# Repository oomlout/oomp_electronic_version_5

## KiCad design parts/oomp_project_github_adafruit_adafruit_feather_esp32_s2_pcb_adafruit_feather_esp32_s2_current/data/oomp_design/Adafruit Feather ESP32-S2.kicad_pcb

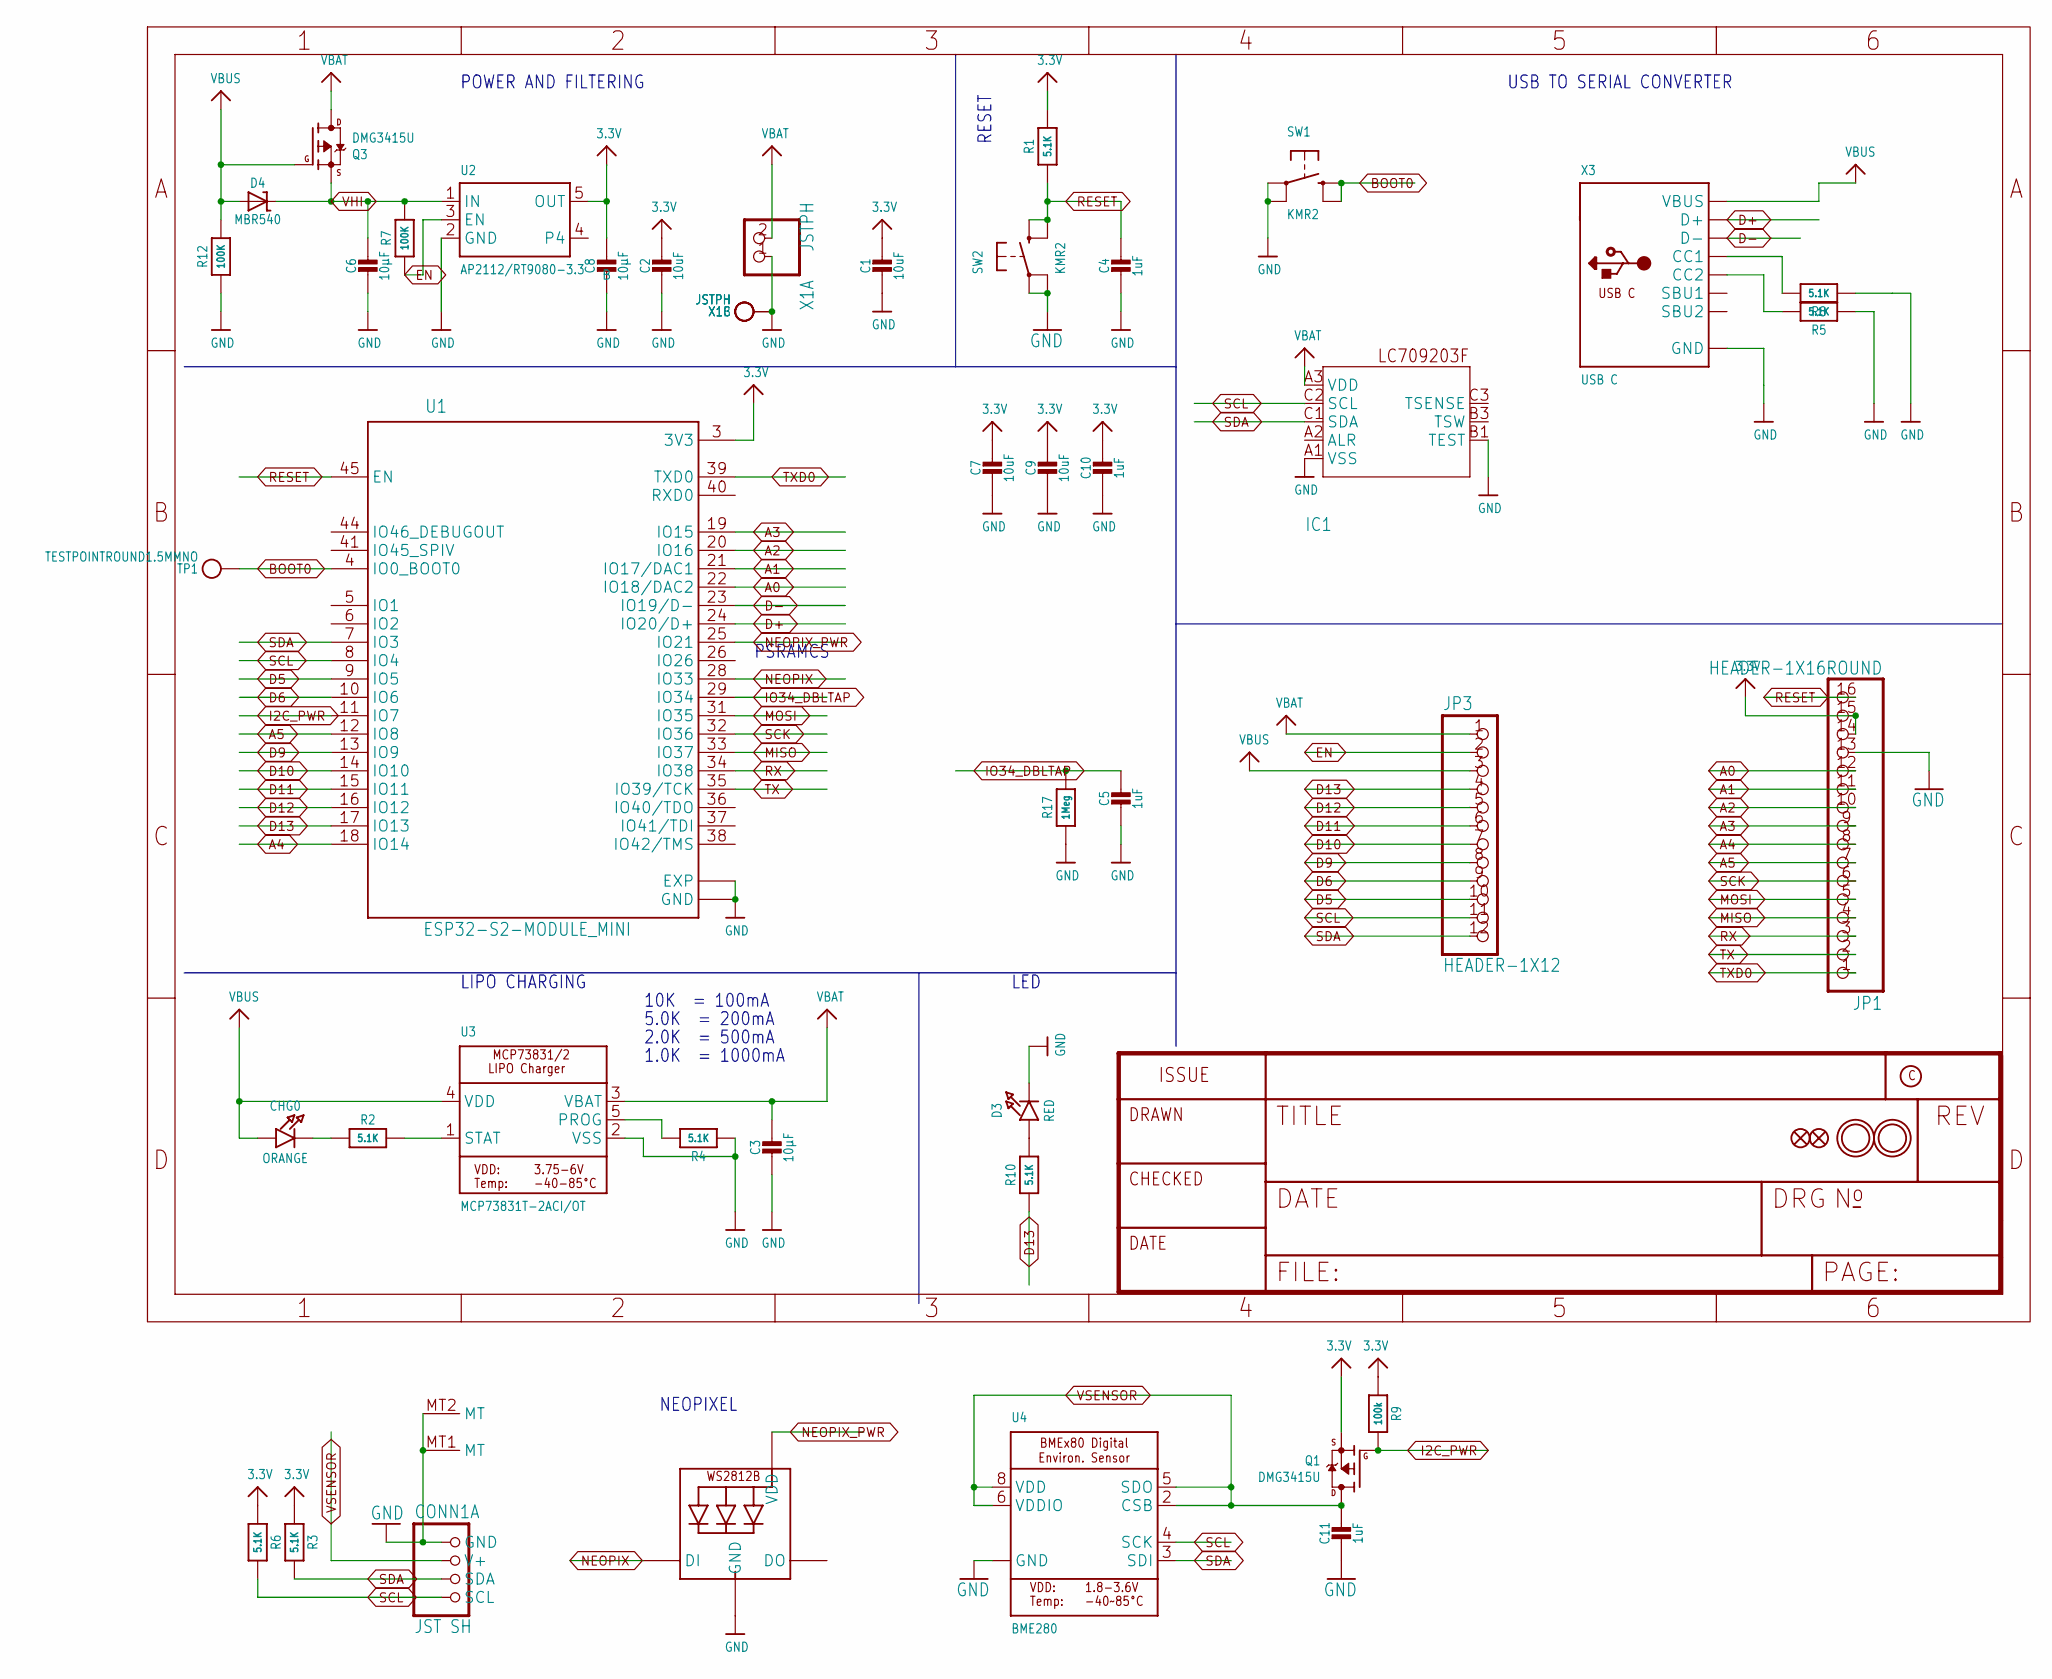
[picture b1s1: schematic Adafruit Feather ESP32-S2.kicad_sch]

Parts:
C1, C2, C7, C9: 10uF; 0805-NO
C3, C6, C8: 10µF; 0805-NO
C4, C5, C10, C11: 1uF; 0603-NO
CHG0: ORANGE; CHIPLED_0603_NOOUTLINE
CONN1: JST SH; JST_SH4_RA
D3: RED; CHIPLED_0603_NOOUTLINE
D4: MBR540; SOD-123
IC1: LC709203F/MH; WLCSP9
JP1: HEADER-1X16ROUND; 1X16_ROUND
JP3: HEADER-1X12; 1X12_ROUND
LED1: WS2812B_SK6805_1515; SK6805_1515
Q1, Q3: DMG3415U; SOT23-R
R1, R2, R3, R4, R5, R6, R8, R10: 5.1K; 0603-NO
R7, R12: 100K; 0603-NO
R9: 100k; 0603-NO
R17: 1Meg; 0603-NO
SW1, SW2: KMR2; BTN_KMR2_4.6X2.8
TP1: TESTPOINTROUND1.5MMNO; TESTPOINT_ROUND_1.5MM_NO
U1: ESP32-S2-MODULE_MINI; QFN60_ESP32-S2-MINI-1_EXP
U2: AP2112/RT9080-3.3; SOT23-5
U3: MCP73831T-2ACI/OT; SOT23-5
U4: BME280
U$31, U$32: MOUNTINGHOLE2.5; MOUNTINGHOLE_2.5_PLATED
U$34, U$35: FIDUCIAL_1MM
X1: JSTPH; JSTPH2_BATT
X3: USB C; USB_C_CUSB31-CFM2AX-01-X

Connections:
3.3V: C1.1, C2.1, C7.1, C8.1, C9.1, C10.1, JP1.14, JP1.15, Q1.2 (S), R1.2, R3.1, R6.1, R9.2, U1.3 (3V3), U2.5 (OUT)
A0: JP1.12, U1.22 (IO18/DAC2)
A1: JP1.11, U1.21 (IO17/DAC1)
A2: JP1.10, U1.20 (IO16)
A3: JP1.9, U1.19 (IO15)
A4: JP1.8, U1.18 (IO14)
A5: JP1.7, U1.12 (IO8)
BOOT0: SW1.B (S), SW1.B' (S1), TP1.P$1, U1.4 (IO0_BOOT0)
D5: JP3.10, U1.9 (IO5)
D6: JP3.9, U1.10 (IO6)
D9: JP3.8, U1.13 (IO9)
D10: JP3.7, U1.14 (IO10)
D11: JP3.6, U1.15 (IO11)
D12: JP3.5, U1.16 (IO12)
D13: JP3.4, R10.1, U1.17 (IO13)
D+: U1.24 (IO20/D+), X3.A6 (D+), X3.B6 (D+)
D-: U1.23 (IO19/D-), X3.A7 (D-), X3.B7 (D-)
EN: JP3.2, R7.1, U2.3 (EN)
GND: C1.2, C2.2, C3.2, C4.2, C5.2, C6.2, C7.2, C8.2, C9.2, C10.2, C11.2, CONN1.1 (GND), CONN1.MT1 (MT), CONN1.MT2 (MT), D3.C, IC1.A1 (VSS), IC1.B1 (TEST), JP1.13, LED1.4 (GND), R4.1, R5.1, R8.1, R12.1, R17.1, SW1.A, SW1.A' (P1), SW2.A, SW2.A' (P1), U1.1 (GND), U1.2 (GND), U1.30 (GND), U1.42 (GND), U1.43 (GND), U1.46 (GND), U1.47 (GND), U1.48 (GND), U1.49 (GND), U1.50 (GND), U1.51 (GND), U1.52 (GND), U1.53 (GND), U1.54 (GND), U1.55 (GND), U1.56 (GND), U1.57 (GND), U1.58 (GND), U1.59 (GND), U1.60 (GND), U1.61 (EXP), U1.62 (EXP), U1.63 (EXP), U1.64 (EXP), U1.65 (EXP), U1.66 (EXP), U1.67 (EXP), U1.68 (EXP), U1.69 (EXP), U1.70 (EXP), U1.71 (EXP), U1.72 (EXP), U1.73 (EXP), U2.2 (GND), U3.2 (VSS), U4.1 (GND), U4.7 (GND), X1.1, X1.NC1, X1.NC2, X3.A1B12 (GND), X3.B1A12 (GND)
I2C_PWR: Q1.1 (G), R9.1, U1.11 (IO7)
IO34_DBLTAP: C5.1, R17.2, U1.29 (IO34)
MISO: JP1.4, U1.33 (IO37)
MOSI: JP1.5, U1.31 (IO35)
unnamed: CHG0.C, R2.1
unnamed: R2.2, U3.1 (STAT)
unnamed: R4.2, U3.5 (PROG)
unnamed: D3.A, R10.2
unnamed: R8.2, X3.A5 (CC1)
unnamed: R5.2, X3.B5 (CC2)
NEOPIX: LED1.1 (DI), U1.28 (IO33)
NEOPIX_PWR: LED1.2 (VDD), U1.25 (IO21)
RESET: C4.1, JP1.16, R1.1, SW2.B (S), SW2.B' (S1), U1.45 (EN)
RX: JP1.3, U1.34 (IO38)
SCK: JP1.6, U1.32 (IO36)
SCL: CONN1.4 (SCL), IC1.C2 (SCL), JP3.11, R6.2, U1.8 (IO4), U4.4 (SCK)
SDA: CONN1.3 (SDA), IC1.C1 (SDA), JP3.12, R3.2, U1.7 (IO3), U4.3 (SDI)
TX: JP1.2, U1.35 (IO39/TCK)
TXD0: JP1.1, U1.39 (TXD0)
VBAT: C3.1, IC1.A3 (VDD), JP3.1, Q3.3 (D), U3.3 (VBAT), X1.2
VBUS: CHG0.A, D4.A, JP3.3, Q3.1 (G), R12.2, U3.4 (VDD), X3.A4B9 (VBUS), X3.B4A9 (VBUS)
VHI: C6.1, D4.C, Q3.2 (S), R7.2, U2.1 (IN)
VSENSOR: C11.1, CONN1.2 (V+), Q1.3 (D), U4.2 (CSB), U4.5 (SDO), U4.6 (VDDIO), U4.8 (VDD)

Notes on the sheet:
1.0K = 1000mA
NEOPIXEL
5.0K = 200mA
LED
USB TO SERIAL CONVERTER
LIPO CHARGING
POWER AND FILTERING
2.0K = 500mA
10K = 100mA
RESET
PSRAMCS

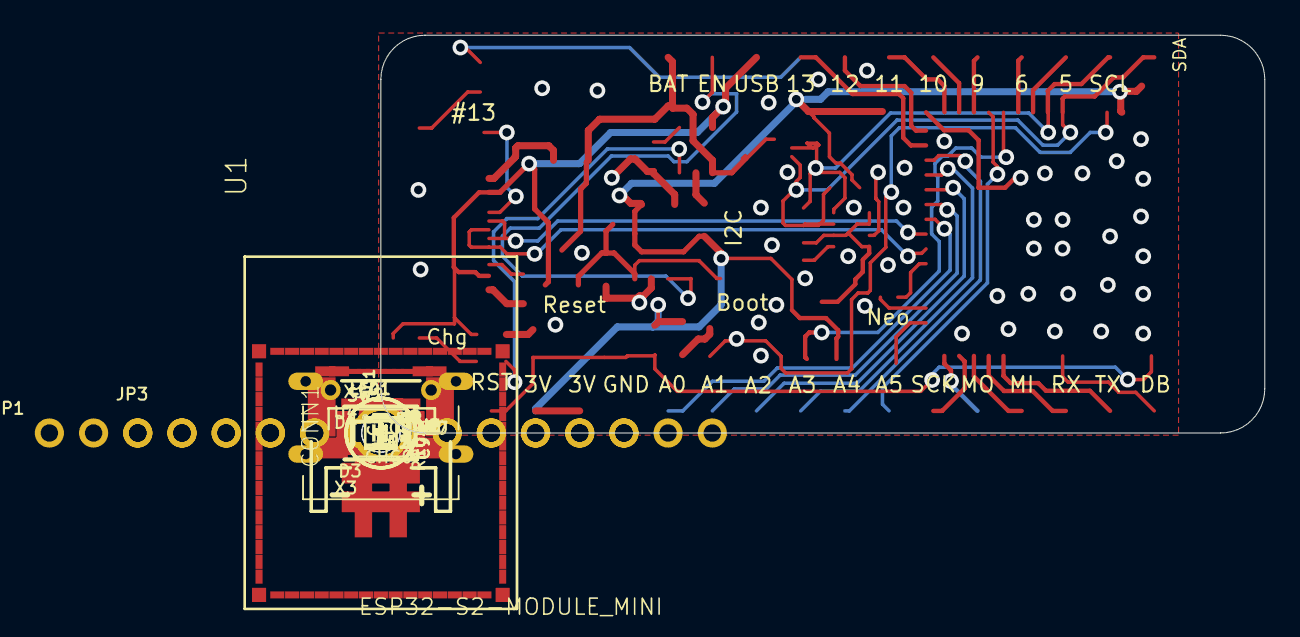
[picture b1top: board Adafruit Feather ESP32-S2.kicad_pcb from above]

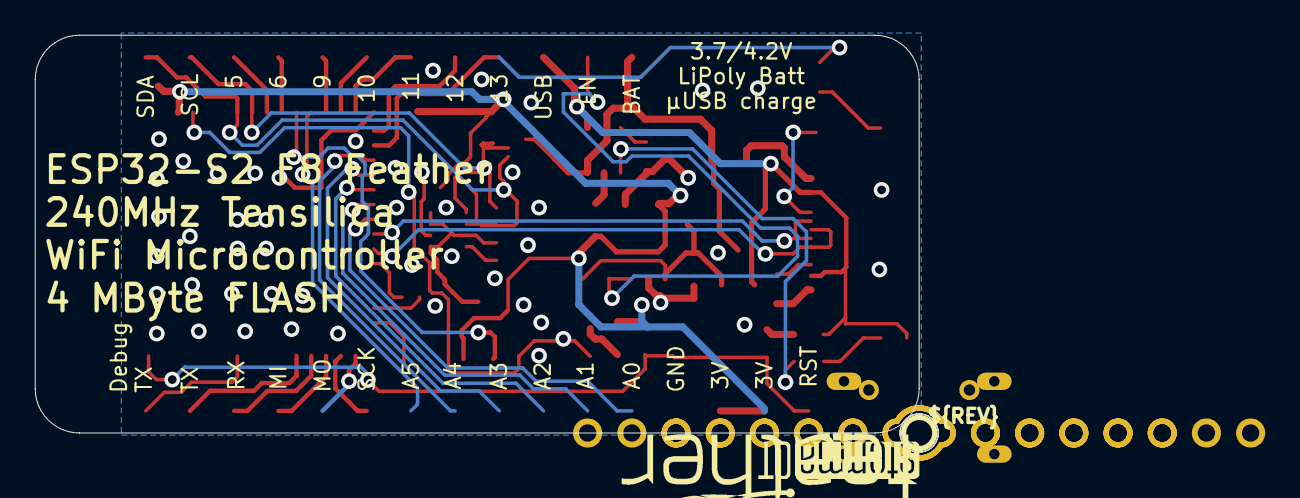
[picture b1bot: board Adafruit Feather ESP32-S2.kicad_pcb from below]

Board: 2 copper layers, 50.8 x 22.9 mm, 51 parts (4 on the bottom side), 42 nets.

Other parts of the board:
U$14: PCBFEAT-REV-040
U$15: FEATHERLOGO_MED
U$53: STEMMAQT
UNK_HOLE_0: dummyfp0
UNK_HOLE_1: dummyfp1

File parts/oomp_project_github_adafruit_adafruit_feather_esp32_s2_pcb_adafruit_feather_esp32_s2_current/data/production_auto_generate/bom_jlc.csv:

Comment,Designator,Footprint,LCSC Part #
,JP3,Adafruit Feather ESP32-S2-import-fps:1X12_ROUND,C7501588
,JP1,Adafruit Feather ESP32-S2-import-fps:1X16_ROUND,C7501270
,U$15,Adafruit Feather ESP32-S2-import-fps:FEATHERLOGO_MED,
,U$14,Adafruit Feather ESP32-S2-import-fps:PCBFEAT-REV-040,
,U$53,Adafruit Feather ESP32-S2-import-fps:STEMMAQT,
,TP1,Adafruit Feather ESP32-S2-import-fps:TESTPOINT_ROUND_1.5MM_NO,
100K,"R7,R12",Adafruit Feather ESP32-S2-import-fps:0603-NO,C25803
100k,R9,Adafruit Feather ESP32-S2-import-fps:0603-NO,C25803
10uF,"C1,C2,C7,C9",Adafruit Feather ESP32-S2-import-fps:0805-NO,
10µF,"C3,C6,C8",Adafruit Feather ESP32-S2-import-fps:0805-NO,
1Meg,R17,Adafruit Feather ESP32-S2-import-fps:0603-NO,C2907003
1uF,"C4,C5,C10,C11",Adafruit Feather ESP32-S2-import-fps:0603-NO,C5673
5.1K,"R1,R2,R3,R4,R5,R6,R8,R10",Adafruit Feather ESP32-S2-import-fps:0603-NO,C23186
AP2112/RT9080-3.3,U2,Adafruit Feather ESP32-S2-import-fps:SOT23-5,
BME280,U4,Adafruit Feather ESP32-S2-import-fps:BME280,
DMG3415U,"Q1,Q3",Adafruit Feather ESP32-S2-import-fps:SOT23-R,
ESP32-S2-MODULE_MINI,U1,Adafruit Feather ESP32-S2-import-fps:QFN60_ESP32-S2-MINI-1_EXP,
FIDUCIAL_1MM,"U$34,U$35",Adafruit Feather ESP32-S2-import-fps:FIDUCIAL_1MM,
JST SH,CONN1,Adafruit Feather ESP32-S2-import-fps:JST_SH4_RA,
JSTPH,X1,Adafruit Feather ESP32-S2-import-fps:JSTPH2_BATT,
KMR2,"SW1,SW2",Adafruit Feather ESP32-S2-import-fps:BTN_KMR2_4.6X2.8,
LC709203F/MH,IC1,Adafruit Feather ESP32-S2-import-fps:WLCSP9,
MBR540,D4,Adafruit Feather ESP32-S2-import-fps:SOD-123,
MCP73831T-2ACI/OT,U3,Adafruit Feather ESP32-S2-import-fps:SOT23-5,
ORANGE,CHG0,Adafruit Feather ESP32-S2-import-fps:CHIPLED_0603_NOOUTLINE,
RED,D3,Adafruit Feather ESP32-S2-import-fps:CHIPLED_0603_NOOUTLINE,
USB C,X3,Adafruit Feather ESP32-S2-import-fps:USB_C_CUSB31-CFM2AX-01-X,
WS2812B_SK6805_1515,LED1,Adafruit Feather ESP32-S2-import-fps:SK6805_1515,

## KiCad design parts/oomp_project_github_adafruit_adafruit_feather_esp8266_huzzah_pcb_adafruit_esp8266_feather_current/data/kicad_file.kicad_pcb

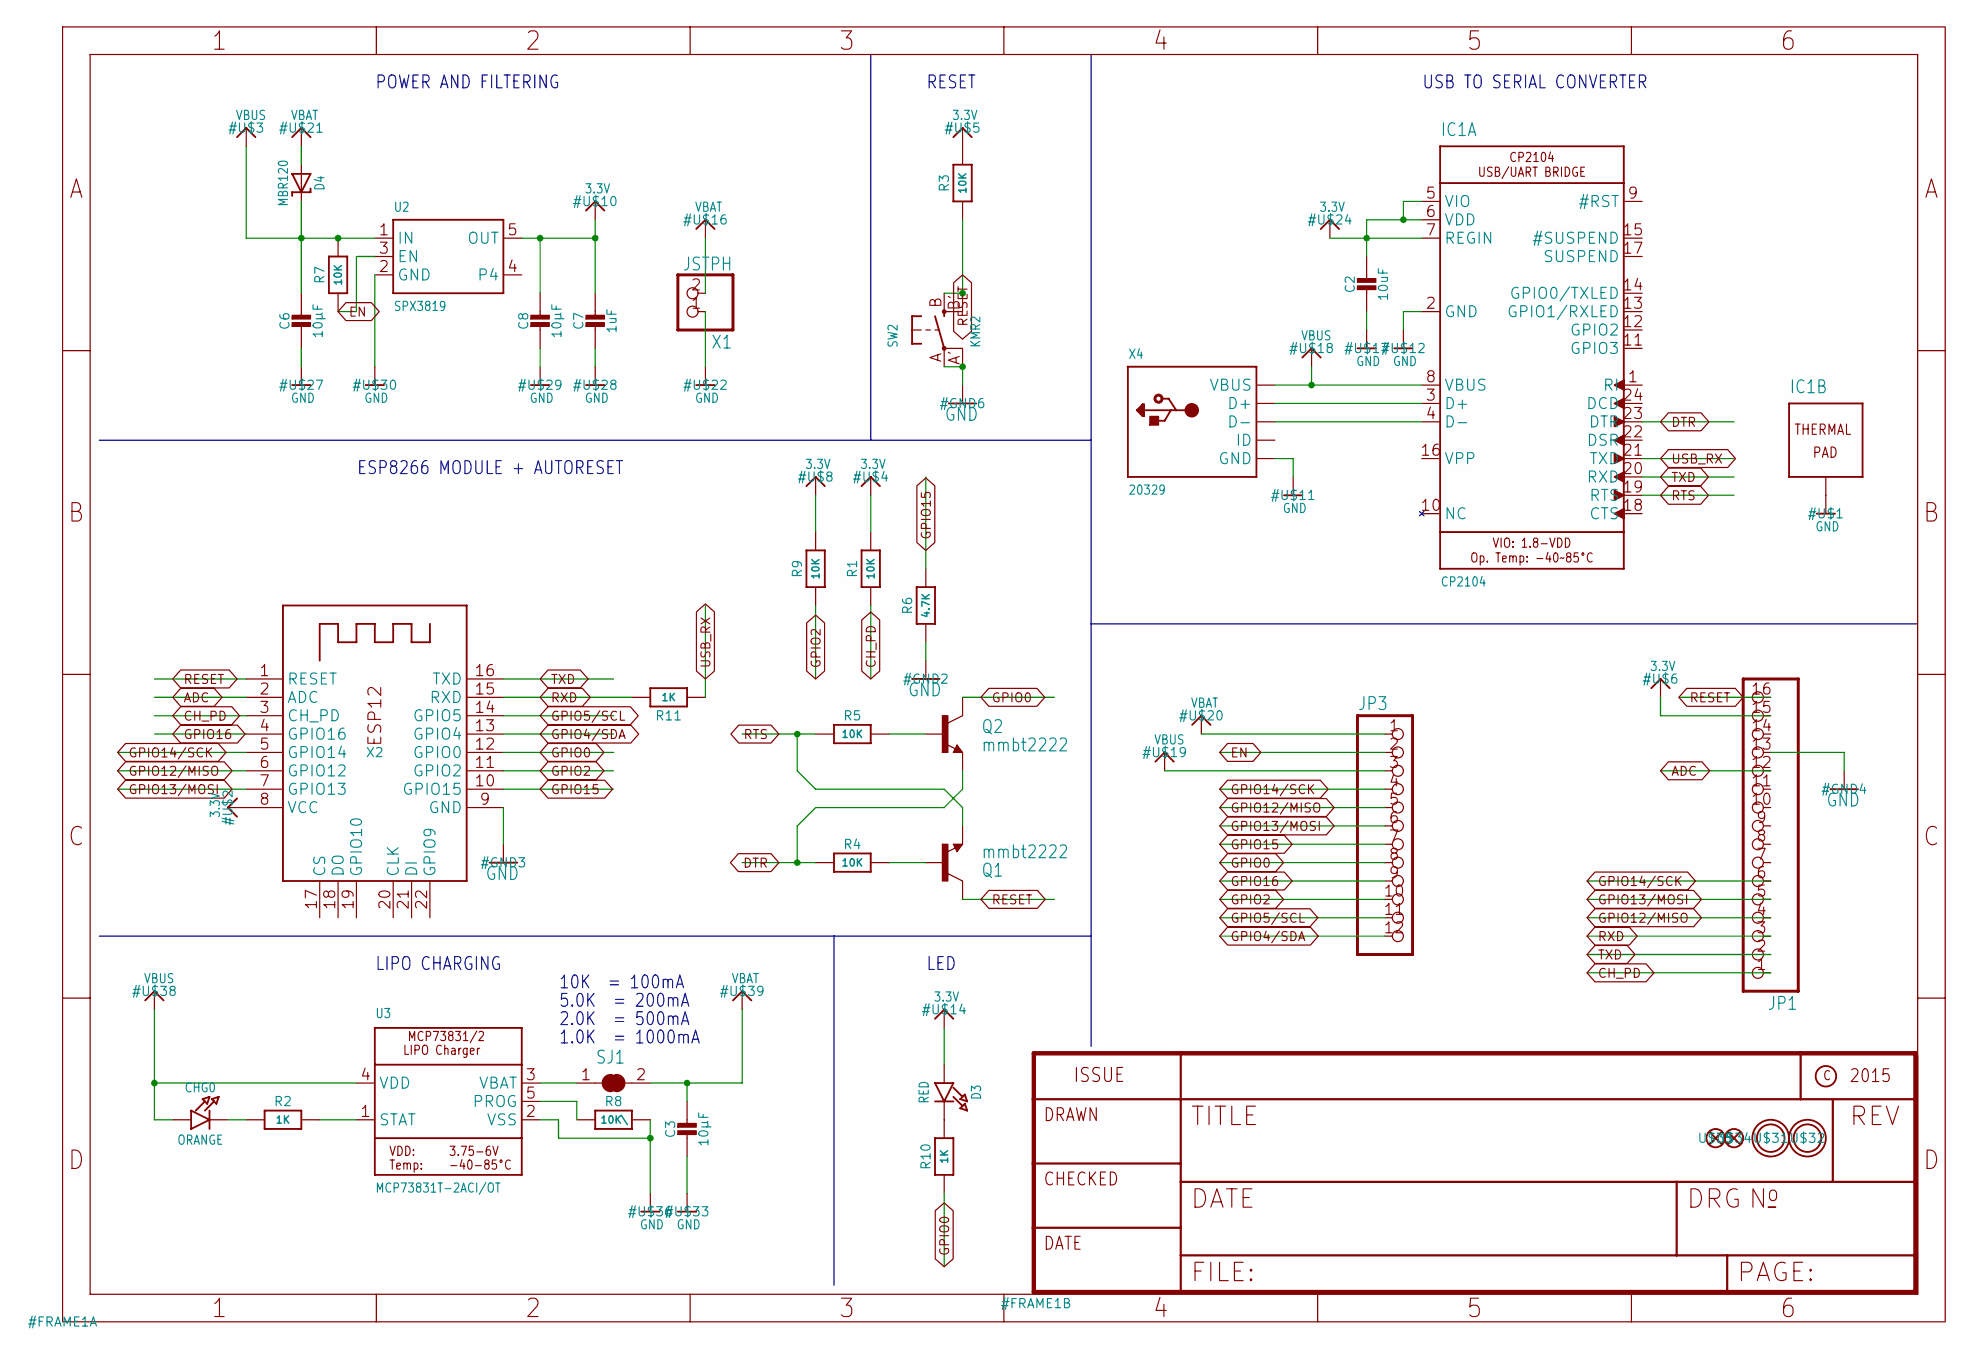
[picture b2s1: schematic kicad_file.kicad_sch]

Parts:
C2: 10uF; 0805-NO
C3, C6, C8: 10µF; 0805-NO
C7: 1uF; 0603-NO
CHG0: ORANGE; CHIPLED_0805_NOOUTLINE
D3: RED; CHIPLED_0805_NOOUTLINE
D4: MBR120; SOD-123
IC1: CP2104; QFN24_4MM_SMSC
JP1: HEADER-1X16ROUND; 1X16_ROUND
JP3: HEADER-1X12; 1X12_ROUND
Q1, Q2: mmbt2222; SOT23-3
R1, R3, R4, R7, R9: 10K; 0603-NO
R2, R10: 1K; 0603-NO
R5: 10K; _0603MP
R6: 4.7K; 0603-NO
R8: 10K\; 0603-NO
R11: 1K; _0603MP
SJ1: SOLDERJUMPER_CLOSED; SOLDERJUMPER_CLOSEDWIRE
SW2: KMR2; BTN_KMR2_4.6X2.8
U2: SPX3819; SOT23-5
U3: MCP73831T-2ACI/OT; SOT23-5
U$31, U$32: MOUNTINGHOLE2.5; MOUNTINGHOLE_2.5_PLATED
U$34, U$35: FIDUCIAL""; FIDUCIAL_1MM
X1: JSTPH; JSTPH2
X2: ESP-12; ESP-12E
X4: 20329; 4UCONN_20329_V2

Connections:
3.3V: C2.1, C7.1, C8.1, D3.A, IC1.5 (VIO), IC1.6 (VDD), IC1.7 (REGIN), JP1.15, R1.2, R3.2, R9.2, U2.5 (OUT), X2.8 (VCC)
ADC: JP1.12, X2.2 (ADC)
CH_PD: JP1.1, R1.1, X2.3 (CH_PD)
DTR: IC1.23 (DTR), Q2.2 (E), R4.1
EN: JP3.2, R7.1, U2.3 (EN)
GND: C2.2, C3.2, C6.2, C7.2, C8.2, IC1.2 (GND), IC1.THERM (TP), JP1.13, R6.1, R8.2, SW2.A, SW2.A' (P1), U2.2 (GND), U3.2 (VSS), X1.1, X2.9 (GND), X4.BASE@1 (GND), X4.BASE@2 (GND), X4.GND, X4.SPRT@1 (GND), X4.SPRT@2 (GND), X4.SPRT@3 (GND), X4.SPRT@4 (GND)
GPIO0: JP3.8, Q2.3 (C), R10.1, X2.12 (GPIO0)
GPIO2: JP3.10, R9.1, X2.11 (GPIO2)
GPIO4/SDA: JP3.12, X2.13 (GPIO4)
GPIO5/SCL: JP3.11, X2.14 (GPIO5)
GPIO12/MISO: JP1.4, JP3.5, X2.6 (GPIO12)
GPIO13/MOSI: JP1.5, JP3.6, X2.7 (GPIO13)
GPIO14/SCK: JP1.6, JP3.4, X2.5 (GPIO14)
GPIO15: JP3.7, R6.2, X2.10 (GPIO15)
GPIO16: JP3.9, X2.4 (GPIO16)
unnamed: CHG0.C, R2.1
unnamed: IC1.3 (D+), X4.D+
unnamed: R2.2, U3.1 (STAT)
unnamed: R8.1, U3.5 (PROG)
unnamed: D3.C, R10.2
unnamed: IC1.4 (D-), X4.D-
unnamed: SJ1.1, U3.3 (VBAT)
unnamed: Q1.1 (B), R4.2
unnamed: Q2.1 (B), R5.2
RESET: JP1.16, Q1.3 (C), R3.1, SW2.B (S), SW2.B' (S1), X2.1 (RESET)
RTS: IC1.19 (RTS), Q1.2 (E), R5.1
RXD: JP1.3, R11.2, X2.15 (RXD)
TXD: IC1.20 (RXD), JP1.2, X2.16 (TXD)
USB_RX: IC1.21 (TXD), R11.1
VBAT: C3.1, D4.A, JP3.1, SJ1.2, X1.2
VBUS: C6.1, CHG0.A, D4.C, IC1.8 (VBUS), JP3.3, R7.2, U2.1 (IN), U3.4 (VDD), X4.VBUS

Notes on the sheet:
5.0K = 200mA
POWER AND FILTERING
LIPO CHARGING
LED
1.0K = 1000mA
10K = 100mA
USB TO SERIAL CONVERTER
ESP8266 MODULE + AUTORESET
RESET
2.0K = 500mA

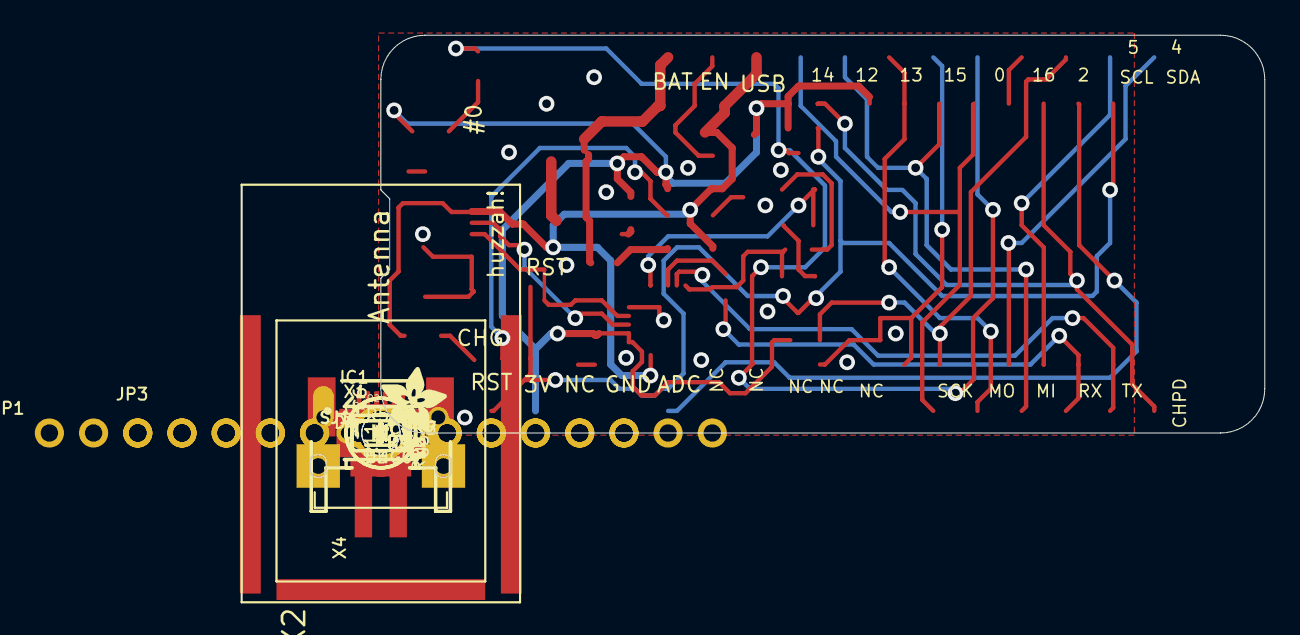
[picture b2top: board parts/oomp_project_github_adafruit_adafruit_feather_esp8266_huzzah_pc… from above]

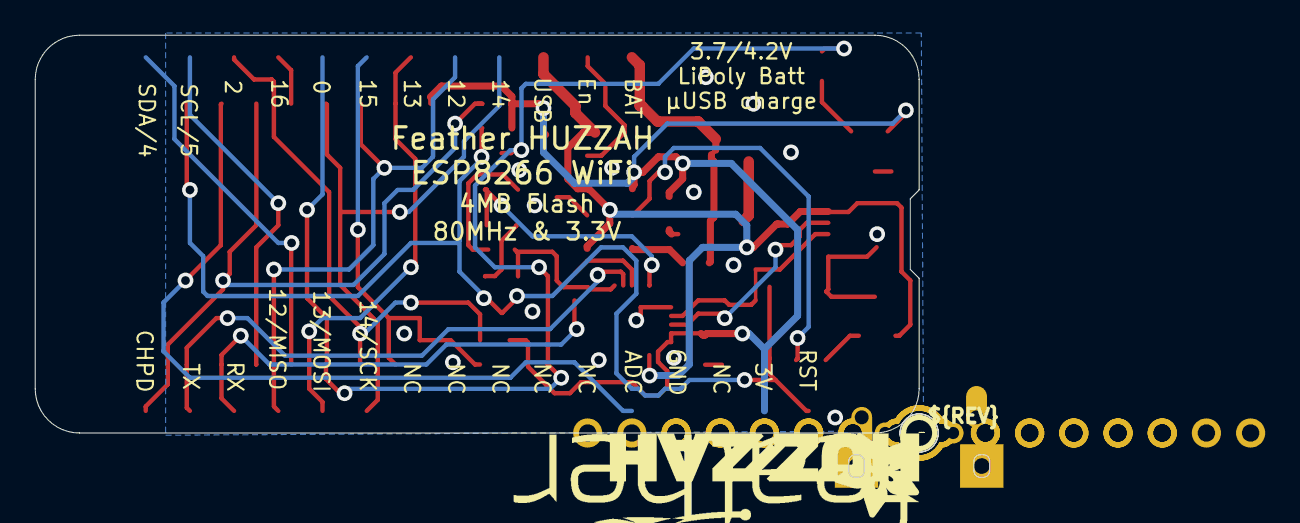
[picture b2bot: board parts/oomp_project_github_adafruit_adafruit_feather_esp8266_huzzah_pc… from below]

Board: 2 copper layers, 50.8 x 22.9 mm, 42 parts (4 on the bottom side), 31 nets.

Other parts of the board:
U$7: ADAFRUIT_5MM
U$9: FEATHERLOGO
U$13: PCBFEAT-REV-040
U$15: ADAFRUIT_3.5MM
U$23: HUZZAHLOGO
UNK_HOLE_0: dummyfp0
UNK_HOLE_1: dummyfp1

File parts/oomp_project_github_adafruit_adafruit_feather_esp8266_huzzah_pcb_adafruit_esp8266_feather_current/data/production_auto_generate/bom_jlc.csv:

Comment,Designator,Footprint,LCSC Part #
,JP3,Adafruit ESP8266 Feather-import-fps:1X12_ROUND,C7501588
,JP1,Adafruit ESP8266 Feather-import-fps:1X16_ROUND,C7501270
,U$15,Adafruit ESP8266 Feather-import-fps:ADAFRUIT_3.5MM,
,U$7,Adafruit ESP8266 Feather-import-fps:ADAFRUIT_5MM,
,U$9,Adafruit ESP8266 Feather-import-fps:FEATHERLOGO,
,U$23,Adafruit ESP8266 Feather-import-fps:HUZZAHLOGO,
,U$13,Adafruit ESP8266 Feather-import-fps:PCBFEAT-REV-040,
10K,"R1,R3,R4,R7,R9",Adafruit ESP8266 Feather-import-fps:0603-NO,C98220
10K,R5,Adafruit ESP8266 Feather-import-fps:_0603MP,C98220
10K\,R8,Adafruit ESP8266 Feather-import-fps:0603-NO,C98220
10uF,C2,Adafruit ESP8266 Feather-import-fps:0805-NO,
10µF,"C3,C6,C8",Adafruit ESP8266 Feather-import-fps:0805-NO,
1K,"R2,R10",Adafruit ESP8266 Feather-import-fps:0603-NO,C2907002
1K,R11,Adafruit ESP8266 Feather-import-fps:_0603MP,C2907002
1uF,C7,Adafruit ESP8266 Feather-import-fps:0603-NO,C5673
20329,X4,Adafruit ESP8266 Feather-import-fps:4UCONN_20329_V2,
4.7K,R6,Adafruit ESP8266 Feather-import-fps:0603-NO,C23162
CP2104,IC1,Adafruit ESP8266 Feather-import-fps:QFN24_4MM_SMSC,
ESP-12,X2,Adafruit ESP8266 Feather-import-fps:ESP-12E,
"FIDUCIAL""""","U$34,U$35",Adafruit ESP8266 Feather-import-fps:FIDUCIAL_1MM,
JSTPH,X1,Adafruit ESP8266 Feather-import-fps:JSTPH2,
KMR2,SW2,Adafruit ESP8266 Feather-import-fps:BTN_KMR2_4.6X2.8,
MBR120,D4,Adafruit ESP8266 Feather-import-fps:SOD-123,
MCP73831T-2ACI/OT,U3,Adafruit ESP8266 Feather-import-fps:SOT23-5,
mmbt2222,"Q1,Q2",Adafruit ESP8266 Feather-import-fps:SOT23-3,
ORANGE,CHG0,Adafruit ESP8266 Feather-import-fps:CHIPLED_0805_NOOUTLINE,
RED,D3,Adafruit ESP8266 Feather-import-fps:CHIPLED_0805_NOOUTLINE,
SPX3819,U2,Adafruit ESP8266 Feather-import-fps:SOT23-5,

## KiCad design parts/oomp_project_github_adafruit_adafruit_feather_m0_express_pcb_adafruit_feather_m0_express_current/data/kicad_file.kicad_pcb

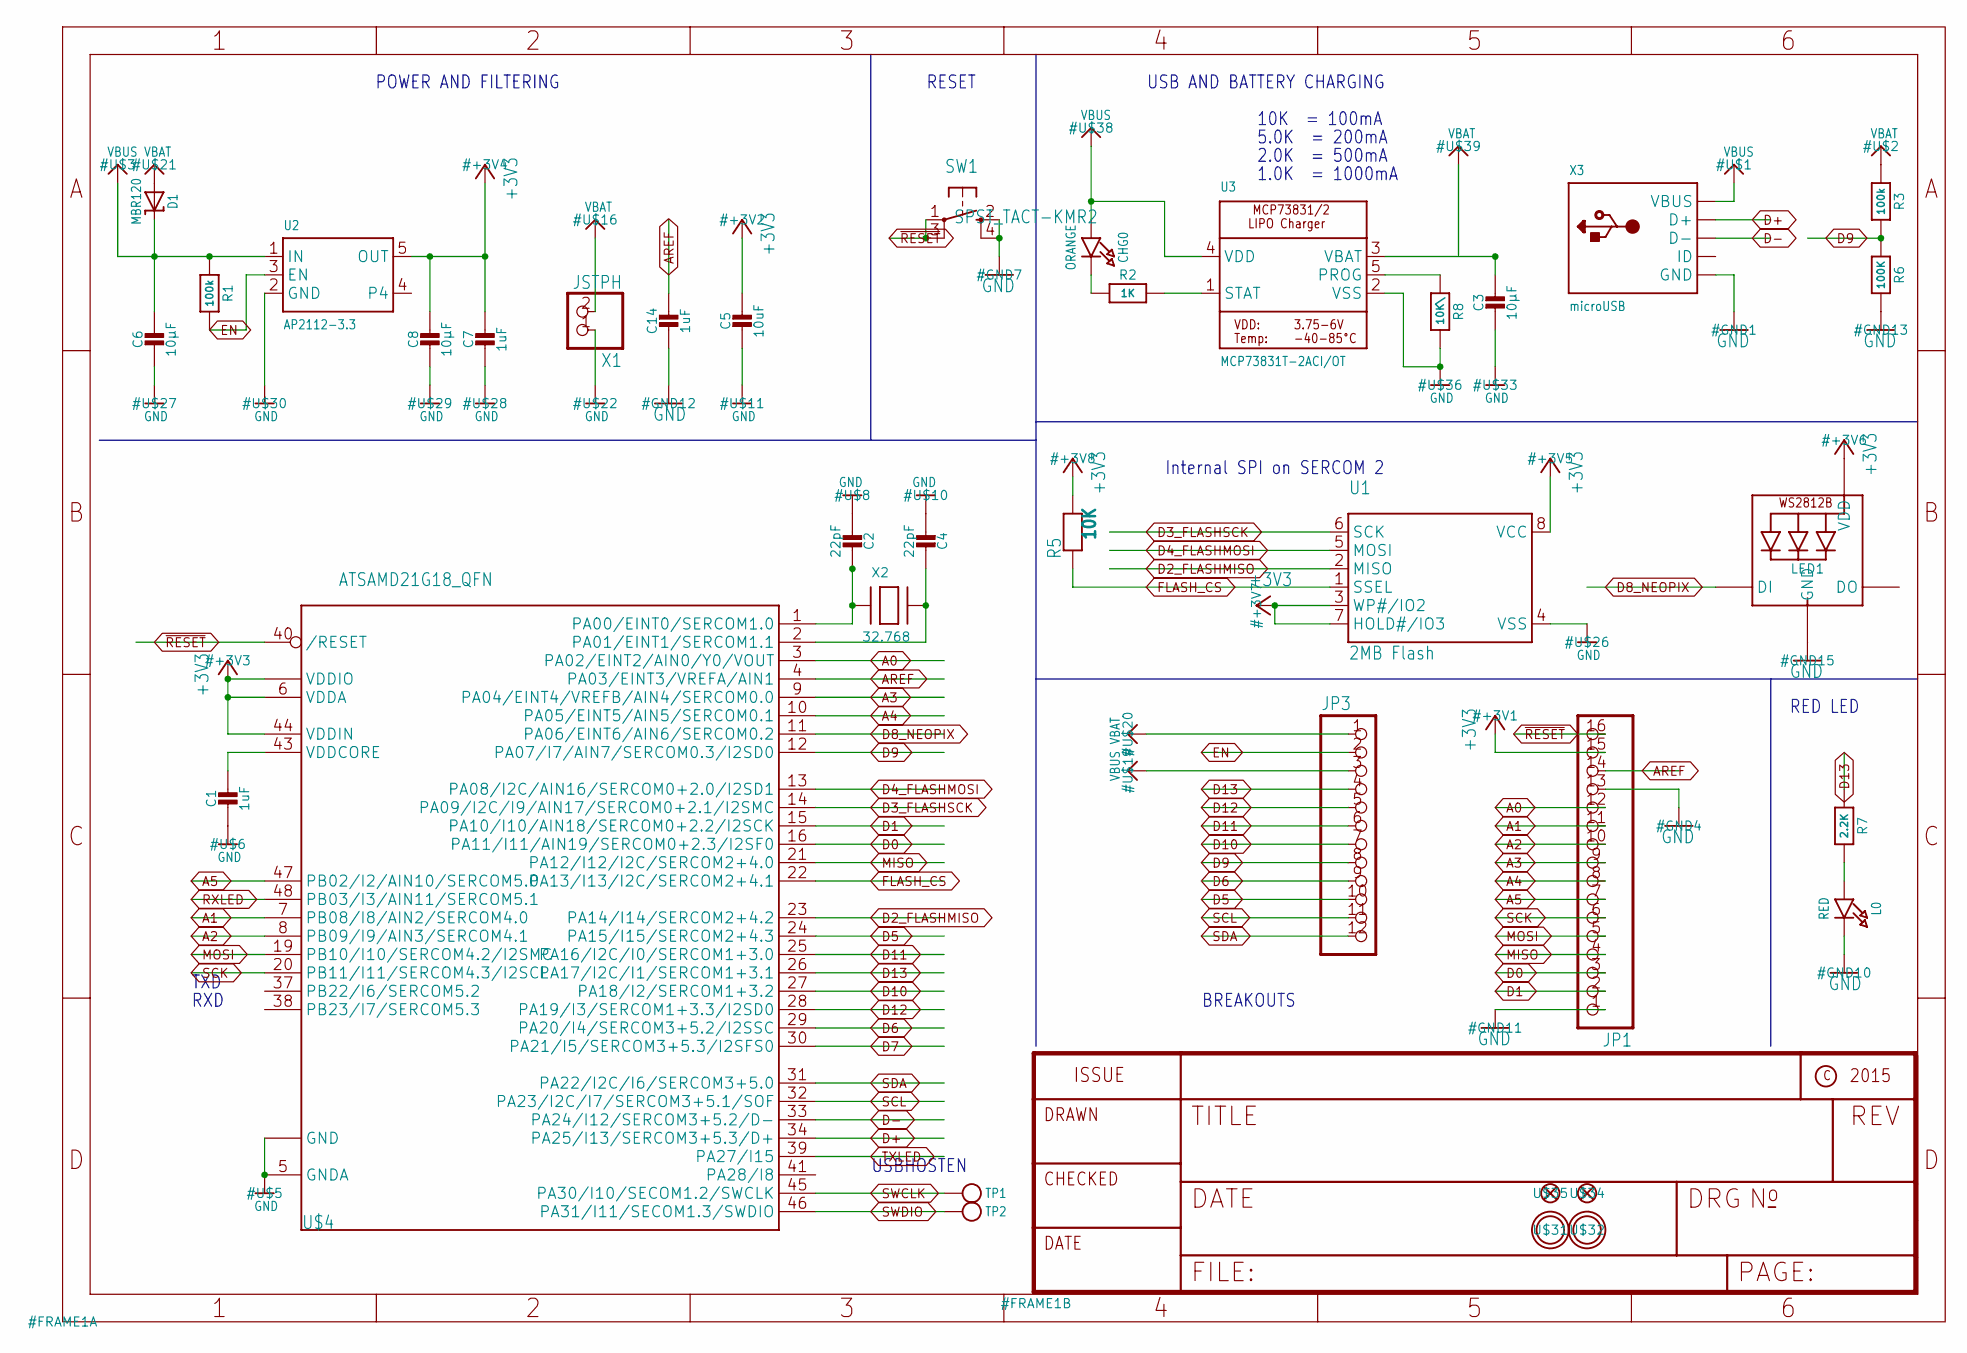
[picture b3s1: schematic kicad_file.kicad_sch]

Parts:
C1, C7, C14: 1uF; 0603-NO
C2, C4: 22pF; 0603-NO
C3, C6, C8: 10µF; 0805-NO
C5: 10uF; 0805-NO
CHG0: ORANGE; CHIPLED_0805_NOOUTLINE
D1: MBR120; SOD-123
JP1: HEADER-1X16ROUND; 1X16_ROUND
JP3: HEADER-1X12; 1X12_ROUND
L0: RED; CHIPLED_0805_NOOUTLINE
LED1: WS2812B3535; LED3535
R1, R3: 100k; 0603-NO
R2: 1K; 0603-NO
R5: 10K; 0603-NO
R6: 100K; 0603-NO
R7: 2.2K; 0603-NO
R8: 10K\; 0603-NO
SW1: SPST_TACT-KMR2; KMR2
TP1, TP2: TESTPOINTROUND1.5MM; TESTPOINT_ROUND_1.5MM
U1: 2MB Flash; SOIC8_208MIL
U2: AP2112-3.3; SOT23-5
U3: MCP73831T-2ACI/OT; SOT23-5
U$4: ATSAMD21G18_QFN; TQFN48_7MM
U$31, U$32: MOUNTINGHOLE2.5; MOUNTINGHOLE_2.5_PLATED
U$34, U$35: FIDUCIAL""; FIDUCIAL_1MM
X1: JSTPH; JSTPH2
X2: 32.768; XTAL3215
X3: microUSB; 4UCONN_20329_V2

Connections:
+3V3: C5.1, C7.1, C8.1, JP1.15, LED1.2 (VDD), R5.2, U1.3 (WP#/IO2), U1.7 (HOLD#/IO3), U1.8 (VCC), U2.5 (OUT), U$4.6 (VDDA), U$4.17 (VDDIO), U$4.36 (VDDIO), U$4.44 (VDDIN)
A0: JP1.12, U$4.3 (PA02/EINT2/AIN0/Y0/VOUT)
A1: JP1.11, U$4.7 (PB08/I8/AIN2/SERCOM4.0)
A2: JP1.10, U$4.8 (PB09/I9/AIN3/SERCOM4.1)
A3: JP1.9, U$4.9 (PA04/EINT4/VREFB/AIN4/SERCOM0.0)
A4: JP1.8, U$4.10 (PA05/EINT5/AIN5/SERCOM0.1)
A5: JP1.7, U$4.47 (PB02/I2/AIN10/SERCOM5.0)
AREF: C14.1, JP1.14, U$4.4 (PA03/EINT3/VREFA/AIN1)
D0: JP1.3, U$4.16 (PA11/I11/AIN19/SERCOM0+2.3/I2SF0)
D1: JP1.2, U$4.15 (PA10/I10/AIN18/SERCOM0+2.2/I2SCK)
D2_FLASHMISO: U1.2 (MISO), U$4.23 (PA14/I14/SERCOM2+4.2)
D3_FLASHSCK: U1.6 (SCK), U$4.14 (PA09/I2C/I9/AIN17/SERCOM0+2.1/I2SMC)
D4_FLASHMOSI: U1.5 (MOSI), U$4.13 (PA08/I2C/AIN16/SERCOM0+2.0/I2SD1)
D5: JP3.10, U$4.24 (PA15/I15/SERCOM2+4.3)
D6: JP3.9, U$4.29 (PA20/I4/SERCOM3+5.2/I2SSC)
D7: U$4.30 (PA21/I5/SERCOM3+5.3/I2SFS0)
D8_NEOPIX: LED1.1 (DI), U$4.11 (PA06/EINT6/AIN6/SERCOM0.2)
D9: JP3.8, R3.2, R6.1, U$4.12 (PA07/I7/AIN7/SERCOM0.3/I2SD0)
D10: JP3.7, U$4.27 (PA18/I2/SERCOM1+3.2)
D11: JP3.6, U$4.25 (PA16/I2C/I0/SERCOM1+3.0)
D12: JP3.5, U$4.28 (PA19/I3/SERCOM1+3.3/I2SD0)
D13: JP3.4, R7.1, U$4.26 (PA17/I2C/I1/SERCOM1+3.1)
D+: U$4.34 (PA25/I13/SERCOM3+5.3/D+), X3.D+
D-: U$4.33 (PA24/I12/SERCOM3+5.2/D-), X3.D-
EN: JP3.2, R1.2, U2.3 (EN)
FLASH_CS: R5.1, U1.1 (SSEL), U$4.22 (PA13/I13/I2C/SERCOM2+4.1)
GND: C1.2, C2.2, C3.2, C4.2, C5.2, C6.2, C7.2, C8.2, C14.2, JP1.1, JP1.13, L0.C, LED1.4 (GND), R6.2, R8.2, SW1.2 (S), SW1.4 (S1), U1.4 (VSS), U2.2 (GND), U3.2 (VSS), U$4.5 (GNDA), U$4.18 (GND), U$4.35 (GND), U$4.42 (GND), U$4.THERMAL (GND), X1.1, X3.BASE@1 (GND), X3.BASE@2 (GND), X3.GND, X3.SPRT@1 (GND), X3.SPRT@2 (GND), X3.SPRT@3 (GND), X3.SPRT@4 (GND)
MISO: JP1.4, U$4.21 (PA12/I12/I2C/SERCOM2+4.0)
MOSI: JP1.5, U$4.19 (PB10/I10/SERCOM4.2/I2SMC)
unnamed: CHG0.C, R2.1
unnamed: L0.A, R7.2
unnamed: R2.2, U3.1 (STAT)
unnamed: R8.1, U3.5 (PROG)
unnamed: C2.1, U$4.1 (PA00/EINT0/SERCOM1.0), X2.P$1
unnamed: C4.1, U$4.2 (PA01/EINT1/SERCOM1.1), X2.P$2
RXLED: U$4.48 (PB03/I3/AIN11/SERCOM5.1)
SCK: JP1.6, U$4.20 (PB11/I11/SERCOM4.3/I2SCL)
SCL: JP3.11, U$4.32 (PA23/I2C/I7/SERCOM3+5.1/SOF)
SDA: JP3.12, U$4.31 (PA22/I2C/I6/SERCOM3+5.0)
SWCLK: TP1.P$1, U$4.45 (PA30/I10/SECOM1.2/SWCLK)
SWDIO: TP2.P$1, U$4.46 (PA31/I11/SECOM1.3/SWDIO)
TXLED: U$4.39 (PA27/I15)
VBAT: C3.1, D1.A, JP3.1, R3.1, U3.3 (VBAT), X1.2
VBUS: C6.1, CHG0.A, D1.C, JP3.3, R1.1, U2.1 (IN), U3.4 (VDD), X3.VBUS
VDDCORE: C1.1, U$4.43 (VDDCORE)
~RESET: JP1.16, SW1.1, SW1.3 (P1), U$4.40 (/RESET)

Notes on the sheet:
Internal SPI on SERCOM 2
10K = 100mA
RED LED
TXD
5.0K = 200mA
2.0K = 500mA
RXD
1.0K = 1000mA
USBHOSTEN
RESET
BREAKOUTS
USB AND BATTERY CHARGING
POWER AND FILTERING

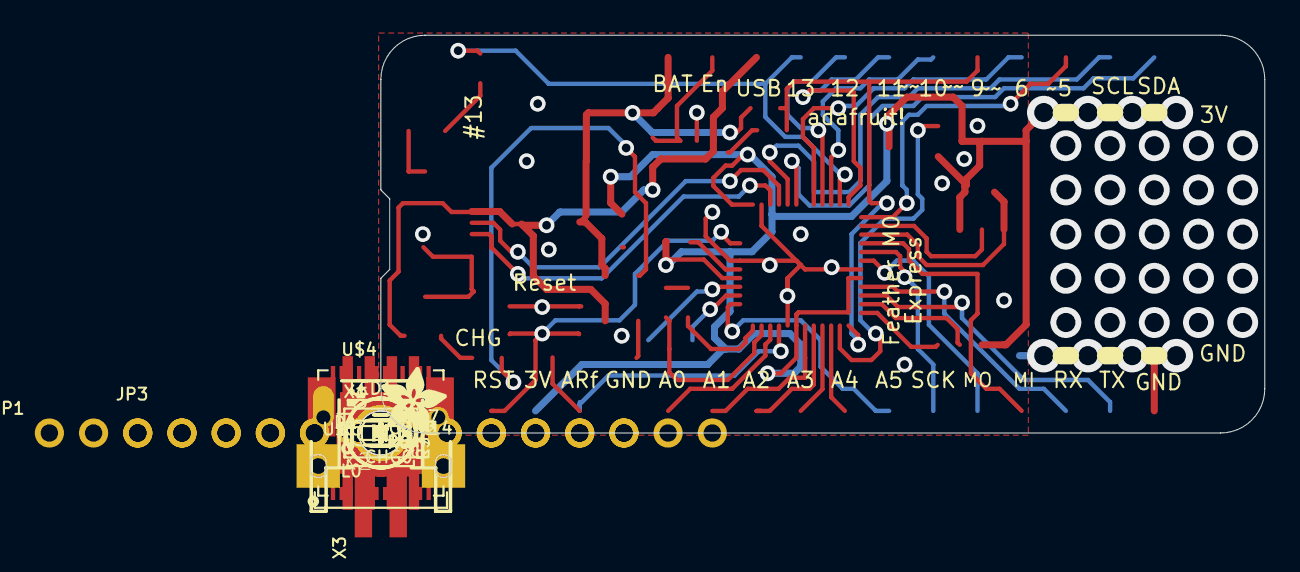
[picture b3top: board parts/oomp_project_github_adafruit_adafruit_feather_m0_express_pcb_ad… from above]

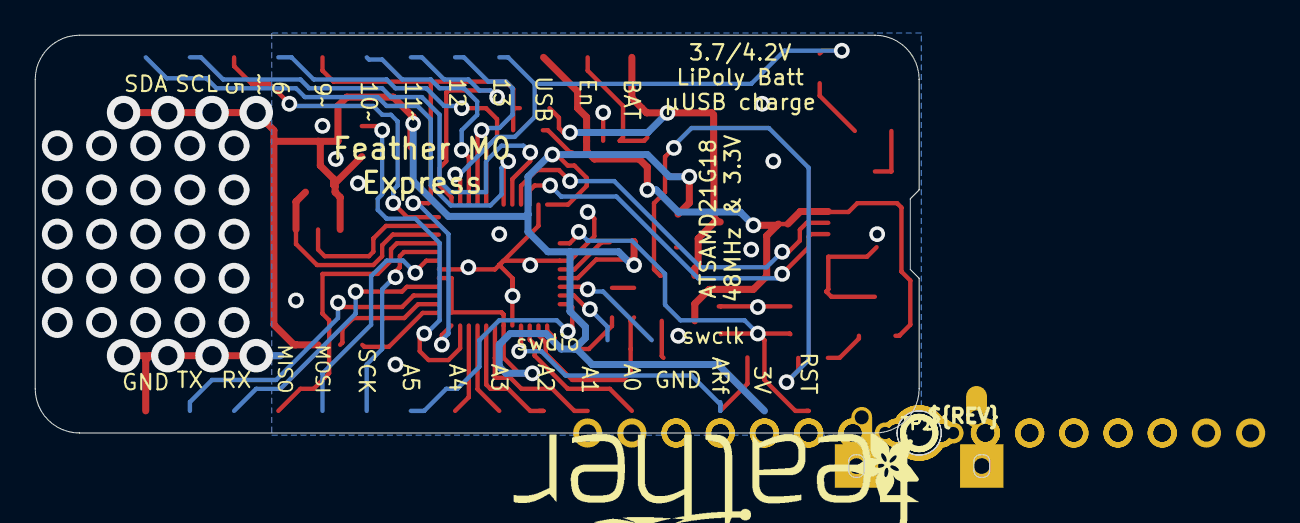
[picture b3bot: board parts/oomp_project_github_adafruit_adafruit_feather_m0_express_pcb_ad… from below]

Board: 2 copper layers, 50.8 x 22.9 mm, 42 parts (5 on the bottom side), 43 nets.

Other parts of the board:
U$7, U$12: ADAFRUIT_3.5MM
U$9: FEATHERLOGO
U$13: PCBFEAT-REV-040
UNK_HOLE_0: dummyfp0
UNK_HOLE_1: dummyfp1

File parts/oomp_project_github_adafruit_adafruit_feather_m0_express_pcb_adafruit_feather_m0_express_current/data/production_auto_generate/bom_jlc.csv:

Comment,Designator,Footprint,LCSC Part #
,JP3,Adafruit Feather M0 Express-import-fps:1X12_ROUND,C7501588
,JP1,Adafruit Feather M0 Express-import-fps:1X16_ROUND,C7501270
,"U$7,U$12",Adafruit Feather M0 Express-import-fps:ADAFRUIT_3.5MM,
,U$9,Adafruit Feather M0 Express-import-fps:FEATHERLOGO,
,U$13,Adafruit Feather M0 Express-import-fps:PCBFEAT-REV-040,
,"TP1,TP2",Adafruit Feather M0 Express-import-fps:TESTPOINT_ROUND_1.5MM,
100k,"R1,R3",Adafruit Feather M0 Express-import-fps:0603-NO,C25803
100K,R6,Adafruit Feather M0 Express-import-fps:0603-NO,C25803
10K,R5,Adafruit Feather M0 Express-import-fps:0603-NO,C98220
10K\,R8,Adafruit Feather M0 Express-import-fps:0603-NO,C98220
10uF,C5,Adafruit Feather M0 Express-import-fps:0805-NO,
10µF,"C3,C6,C8",Adafruit Feather M0 Express-import-fps:0805-NO,
1K,R2,Adafruit Feather M0 Express-import-fps:0603-NO,C2907002
1uF,"C1,C7,C14",Adafruit Feather M0 Express-import-fps:0603-NO,C5673
2.2K,R7,Adafruit Feather M0 Express-import-fps:0603-NO,C4190
22pF,"C2,C4",Adafruit Feather M0 Express-import-fps:0603-NO,C105620
2MB Flash,U1,Adafruit Feather M0 Express-import-fps:SOIC8_208MIL,
32.768,X2,Adafruit Feather M0 Express-import-fps:XTAL3215,
AP2112-3.3,U2,Adafruit Feather M0 Express-import-fps:SOT23-5,
ATSAMD21G18_QFN,U$4,Adafruit Feather M0 Express-import-fps:TQFN48_7MM,
"FIDUCIAL""""","U$34,U$35",Adafruit Feather M0 Express-import-fps:FIDUCIAL_1MM,
JSTPH,X1,Adafruit Feather M0 Express-import-fps:JSTPH2,
MBR120,D1,Adafruit Feather M0 Express-import-fps:SOD-123,
MCP73831T-2ACI/OT,U3,Adafruit Feather M0 Express-import-fps:SOT23-5,
microUSB,X3,Adafruit Feather M0 Express-import-fps:4UCONN_20329_V2,
ORANGE,CHG0,Adafruit Feather M0 Express-import-fps:CHIPLED_0805_NOOUTLINE,
RED,L0,Adafruit Feather M0 Express-import-fps:CHIPLED_0805_NOOUTLINE,
SPST_TACT-KMR2,SW1,Adafruit Feather M0 Express-import-fps:KMR2,
WS2812B3535,LED1,Adafruit Feather M0 Express-import-fps:LED3535,

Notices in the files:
parts and their libraries:
COPYRIGHT: Copyright (C) 2018 Accelerated Designs. All rights reserved
